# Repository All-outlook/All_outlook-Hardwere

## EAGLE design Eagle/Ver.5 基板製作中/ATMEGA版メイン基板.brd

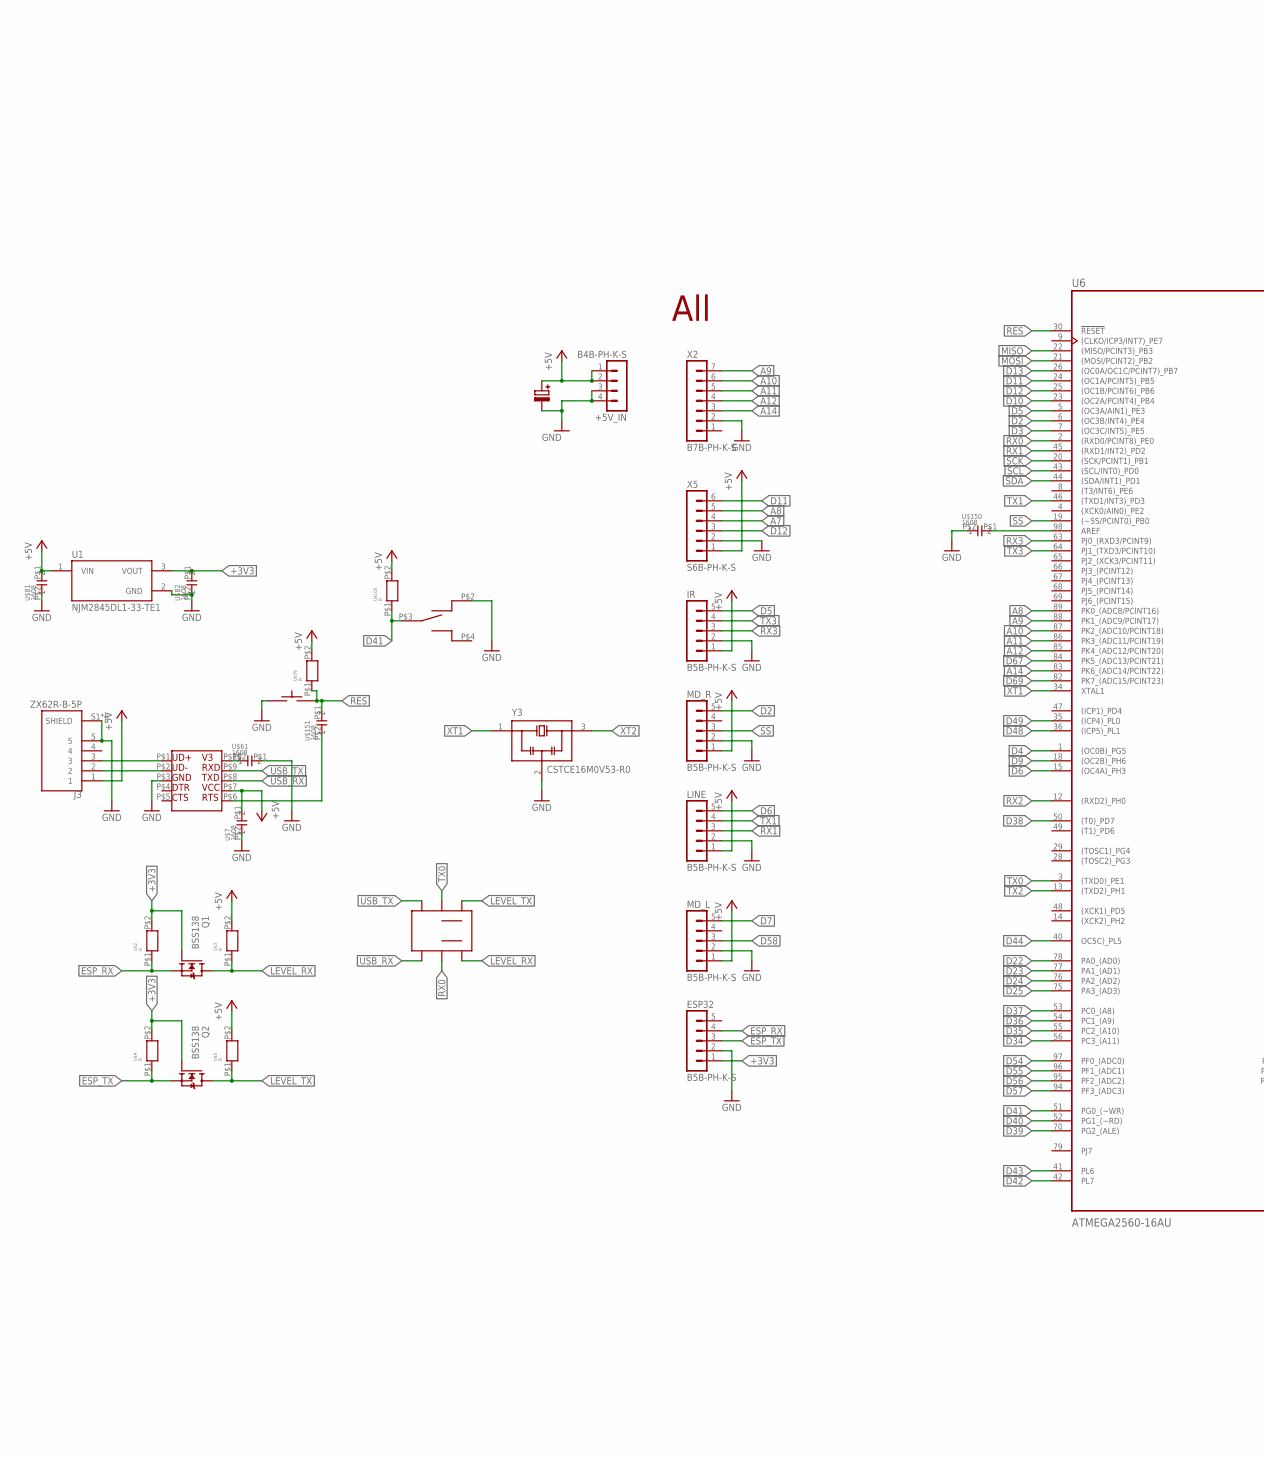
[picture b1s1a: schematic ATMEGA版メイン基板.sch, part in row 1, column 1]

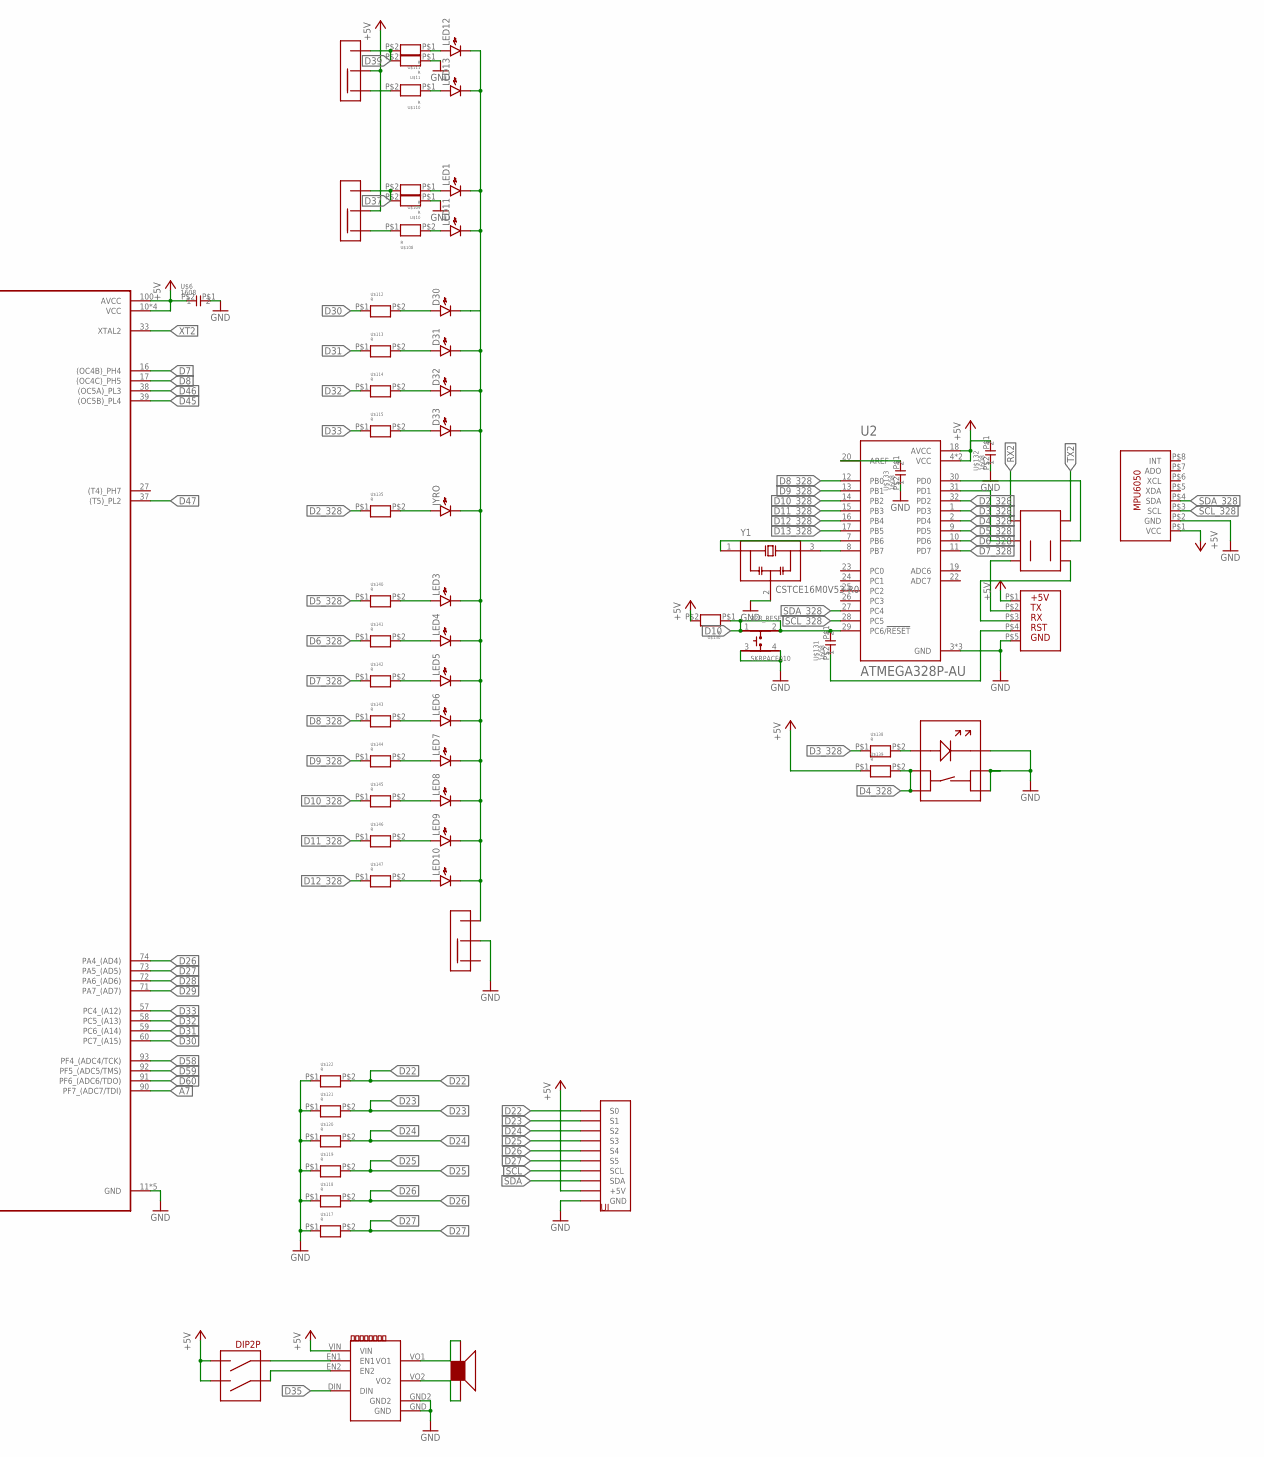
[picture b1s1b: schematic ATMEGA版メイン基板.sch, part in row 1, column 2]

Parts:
328_RESET: SKRPACE010; SW_SKRPACE010
+5V_IN: B4B-PH-K-S
D30, D31, D32, D33: LED1608
ESP32: B5B-PH-K-S
IR: B5B-PH-K-S
J3: ZX62R-B-5P; HRS_ZX62R-B-5P
JYRO: LED1608
LED1, LED3, LED4, LED5, LED6, LED7, LED8, LED9, LED10, LED11, LED12, LED13: LED1608
LINE: B5B-PH-K-S
MD_L: B5B-PH-K-S
MD_R: B5B-PH-K-S
Q1, Q2: BSS138; SOT23
U1: NJM2845DL1-33-TE1; DPAK228P968X238-4N
U2: ATMEGA328P-AU; QFP80P900X900X120-32N
U6: ATMEGA2560-16AU; QFP50P1600X1600X120-100N
U$1: 25V100
U$2, U$3, U$4, U$5, U$10, U$11, U$79, U$105, U$108, U$109, U$110, U$111, U$112, U$113, U$114, U$115, U$117, U$118, U$119, U$120, U$121, U$122, U$130, U$135, U$138, U$139, U$140, U$141, U$142, U$143, U$144, U$145, U$146, U$147: R; 1608
U$6, U$7, U$61, U$81, U$82, U$131, U$132, U$133, U$150, U$151: 1608; CON
U$8, U$136: 2SW
U$9: S
U$12: BUZA-; ぶざー
U$13: BUZA_DR
U$14: DIP2
U$46: CH340K
U$80: TAKUTO; 12
U$93: ジャイロ
U$106, U$107, U$148: SSW
U$134: SI
U$137: SWLED
U$149: UI
U$152: ALL
X2: B7B-PH-K-S
X5: S6B-PH-K-S
Y1, Y3: CSTCE16M0V53-R0; OSC_CSTCE16M0V53-R0

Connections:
+3V3: ESP32.1, Q1.1 (G), Q2.1 (G), U1.3 (VOUT), U$2.P$2, U$4.P$2, U$82.P$1 (1)
+5V: +5V_IN.1, +5V_IN.2, IR.1, J3.1, LINE.1, MD_L.1, MD_R.1, U1.1 (VIN), U2.4 (VCC), U2.6 (VCC), U2.18 (AVCC), U6.10 (VCC), U6.31 (VCC), U6.61 (VCC), U6.80 (VCC), U6.100 (AVCC), U$1.P$1, U$3.P$2, U$5.P$2, U$6.P$2 (2), U$7.P$1 (1), U$13.VIN, U$14.P$15, U$14.P$16, U$46.P$7, U$79.P$2, U$81.P$1 (1), U$93.P$1 (VCC), U$105.P$2, U$106.P$3, U$107.P$3, U$130.P$2, U$132.P$1 (1), U$134.P$1, U$139.P$1, U$149.P$1 (+5V), X5.1
A7: U6.90 (PF7_(ADC7/TDI)), X5.4
A8: U6.89 (PK0_(ADC8/PCINT16)), X5.5
A9: U6.88 (PK1_(ADC9/PCINT17)), X2.7
A10: U6.87 (PK2_(ADC10/PCINT18)), X2.6
A11: U6.86 (PK3_(ADC11/PCINT19)), X2.5
A12: U6.85 (PK4_(ADC12/PCINT20)), X2.4
A14: U6.83 (PK6_(ADC14/PCINT22)), X2.3
D2: MD_R.5, U6.6 ((OC3B/INT4)_PE4)
D2_328: U2.32 (PD2), U$135.P$1
D3: U6.7 ((OC3C/INT5)_PE5)
D3_328: U2.1 (PD3), U$138.P$1
D4: U6.1 ((OC0B)_PG5)
D4_328: U2.2 (PD4), U$137.1, U$137.2, U$139.P$2
D5: IR.5, U6.5 ((OC3A/AIN1)_PE3)
D5_328: U2.9 (PD5), U$140.P$1
D6: LINE.5, U6.15 ((OC4A)_PH3)
D6_328: U2.10 (PD6), U$141.P$1
D7: MD_L.5, U6.16 ((OC4B)_PH4)
D7_328: U2.11 (PD7), U$142.P$1
D8: U6.17 ((OC4C)_PH5)
D8_328: U2.12 (PB0), U$143.P$1
D9: U6.18 ((OC2B)_PH6)
D9_328: U2.13 (PB1), U$144.P$1
D10: 328_RESET.1, 328_RESET.2, U2.29 (PC6/!RESET), U6.23 ((OC2A/PCINT4)_PB4), U$130.P$1, U$131.P$1 (1)
D10_328: U2.14 (PB2), U$145.P$1
D11: U6.24 ((OC1A/PCINT5)_PB5), X5.6
D11_328: U2.15 (PB3), U$146.P$1
D12: U6.25 ((OC1B/PCINT6)_PB6), X5.3
D12_328: U2.16 (PB4), U$147.P$1
D13: U6.26 ((OC0A/OC1C/PCINT7)_PB7)
D13_328: U2.17 (PB5)
D22: U6.78 (PA0_(AD0)), U$122.P$2, U$149.P$3 (S0)
D23: U6.77 (PA1_(AD1)), U$121.P$2, U$149.P$4 (S1)
D24: U6.76 (PA2_(AD2)), U$120.P$2, U$149.P$5 (S2)
D25: U6.75 (PA3_(AD3)), U$119.P$2, U$149.P$6 (S3)
D26: U6.74 (PA4_(AD4)), U$118.P$2, U$149.P$7 (S4)
D27: U6.73 (PA5_(AD5)), U$117.P$2, U$149.P$8 (S5)
D28: U6.72 (PA6_(AD6))
D29: U6.71 (PA7_(AD7))
D30: U6.60 (PC7_(A15)), U$112.P$1
D31: U6.59 (PC6_(A14)), U$113.P$1
D32: U6.58 (PC5_(A13)), U$114.P$1
D33: U6.57 (PC4_(A12)), U$115.P$1
D34: U6.56 (PC3_(A11))
D35: U6.55 (PC2_(A10)), U$13.DIN
D36: U6.54 (PC1_(A9))
D37: U6.53 (PC0_(A8)), U$10.P$2, U$106.P$2, U$109.P$2
D38: U6.50 ((T0)_PD7)
D39: U6.70 (PG2_(ALE)), U$11.P$2, U$107.P$2, U$111.P$2
D40: U6.52 (PG1_(~RD))
D41: U6.51 (PG0_(~WR)), U$9.P$3 (2), U$105.P$1
D42: U6.42 (PL7)
D43: U6.41 (PL6)
D44: U6.40 (OC5C)_PL5)
D45: U6.39 ((OC5B)_PL4)
D46: U6.38 ((OC5A)_PL3)
D47: U6.37 ((T5)_PL2)
D48: U6.36 ((ICP5)_PL1)
D49: U6.35 ((ICP4)_PL0)
D54: U6.97 (PF0_(ADC0))
D55: U6.96 (PF1_(ADC1))
D56: U6.95 (PF2_(ADC2))
D57: U6.94 (PF3_(ADC3))
D58: MD_L.3, U6.93 (PF4_(ADC4/TCK))
D59: U6.92 (PF5_(ADC5/TMS))
D60: U6.91 (PF6_(ADC6/TDO))
D67: U6.84 (PK5_(ADC13/PCINT21))
D69: U6.82 (PK7_(ADC15/PCINT23))
ESP_RX: ESP32.4, Q1.2 (S), U$2.P$1
ESP_TX: ESP32.3, Q2.2 (S), U$4.P$1
GND: 328_RESET.3, 328_RESET.4, +5V_IN.3, +5V_IN.4, ESP32.2, IR.2, J3.5, J3.S1 (SHIELD), J3.S2 (SHIELD), J3.S3 (SHIELD), J3.S4 (SHIELD), J3.S5 (SHIELD), J3.S6 (SHIELD), LINE.2, MD_L.2, MD_R.2, U1.2 (GND), U2.3 (GND), U2.5 (GND), U2.21 (GND), U6.11 (GND), U6.32 (GND), U6.62 (GND), U6.81 (GND), U6.99 (GND), U$1.P$2, U$6.P$1 (1), U$7.P$2 (2), U$9.P$2 (1), U$10.P$1, U$11.P$1, U$13.GND, U$13.GND2, U$46.P$3, U$61.P$1 (1), U$80.P$1, U$80.P$4, U$81.P$2 (2), U$82.P$2 (2), U$93.P$2 (GND), U$117.P$1, U$118.P$1, U$119.P$1, U$120.P$1, U$121.P$1, U$122.P$1, U$132.P$2 (2), U$133.P$2 (2), U$134.P$5, U$137.3, U$137.4, U$137.- (LED-), U$148.P$3, U$149.P$2 (GND), U$150.P$2 (2), X2.2, X5.2, Y1.2 (GND), Y3.2 (GND)
LEVEL_RX: Q1.3 (D), U$3.P$1, U$8.P$1
LEVEL_TX: Q2.3 (D), U$5.P$1, U$8.P$6
MISO: U6.22 ((MISO/PCINT3)_PB3)
MOSI: U6.21 ((MOSI/PCINT2)_PB2)
unnamed: U$12.P$2, U$13.VO2
unnamed: J3.2, U$46.P$2
unnamed: J3.3, U$46.P$1
unnamed: U$46.P$10, U$61.P$2 (2)
unnamed: D30.K, D31.K, D32.K, D33.K, JYRO.K, LED1.K, LED3.K, LED4.K, LED5.K, LED6.K, LED7.K, LED8.K, LED9.K, LED10.K, LED11.K, LED12.K, LED13.K, U$148.P$2
unnamed: LED12.A, U$111.P$1
unnamed: LED13.A, U$110.P$1
unnamed: U$107.P$1, U$110.P$2
unnamed: U$106.P$1, U$108.P$1
unnamed: LED11.A, U$108.P$2
unnamed: LED1.A, U$109.P$1
unnamed: U$12.P$1, U$13.VO1
unnamed: U$13.EN2, U$14.P$1
unnamed: U$13.EN1, U$14.P$2
unnamed: D30.A, U$112.P$2
unnamed: D31.A, U$113.P$2
unnamed: D32.A, U$114.P$2
unnamed: D33.A, U$115.P$2
unnamed: U2.20 (AREF), U$133.P$1 (1)
unnamed: U$131.P$2 (2), U$134.P$4
unnamed: U2.31 (PD1), U$136.P$2
unnamed: U2.8 (PB7), Y1.3 (OUT)
unnamed: U2.7 (PB6), Y1.1 (IN)
unnamed: JYRO.A, U$135.P$2
unnamed: U2.30 (PD0), U$136.P$5
unnamed: U$134.P$3, U$136.P$6
unnamed: U$134.P$2, U$136.P$1
unnamed: U$137.+ (LED+), U$138.P$2
unnamed: LED3.A, U$140.P$2
unnamed: LED4.A, U$141.P$2
unnamed: LED5.A, U$142.P$2
unnamed: LED6.A, U$143.P$2
unnamed: LED7.A, U$144.P$2
unnamed: LED8.A, U$145.P$2
unnamed: LED9.A, U$146.P$2
unnamed: LED10.A, U$147.P$2
unnamed: U6.98 (AREF), U$150.P$1 (1)
unnamed: U$46.P$6, U$151.P$2 (2)
RES: U6.30 (!RESET), U$79.P$1, U$80.P$2, U$80.P$3, U$151.P$1 (1)
RX0: U6.2 ((RXD0/PCINT8)_PE0), U$8.P$2
RX1: LINE.3, U6.45 ((RXD1/INT2)_PD2)
RX2: U6.12 ((RXD2)_PH0), U$136.P$3
RX3: IR.3, U6.63 (PJ0_(RXD3/PCINT9))
SCK: U6.20 ((SCK/PCINT1)_PB1)
SCL: U6.43 ((SCL/INT0)_PD0), U$149.P$9 (SCL)
SCL_328: U2.28 (PC5), U$93.P$3 (SCL)
SDA: U6.44 ((SDA/INT1)_PD1), U$149.P$10 (SDA)
SDA_328: U2.27 (PC4), U$93.P$4 (SDA)
SS: MD_R.3, U6.19 ((~SS/PCINT0)_PB0)
TX0: U6.3 ((TXD0)_PE1), U$8.P$5
TX1: LINE.4, U6.46 ((TXD1/INT3)_PD3)
TX2: U6.13 ((TXD2)_PH1), U$136.P$4
TX3: IR.4, U6.64 (PJ1_(TXD3/PCINT10))
USB_RX: U$8.P$3, U$46.P$8
USB_TX: U$8.P$4, U$46.P$9
XT1: U6.34 (XTAL1), Y3.1 (IN)
XT2: U6.33 (XTAL2), Y3.3 (OUT)

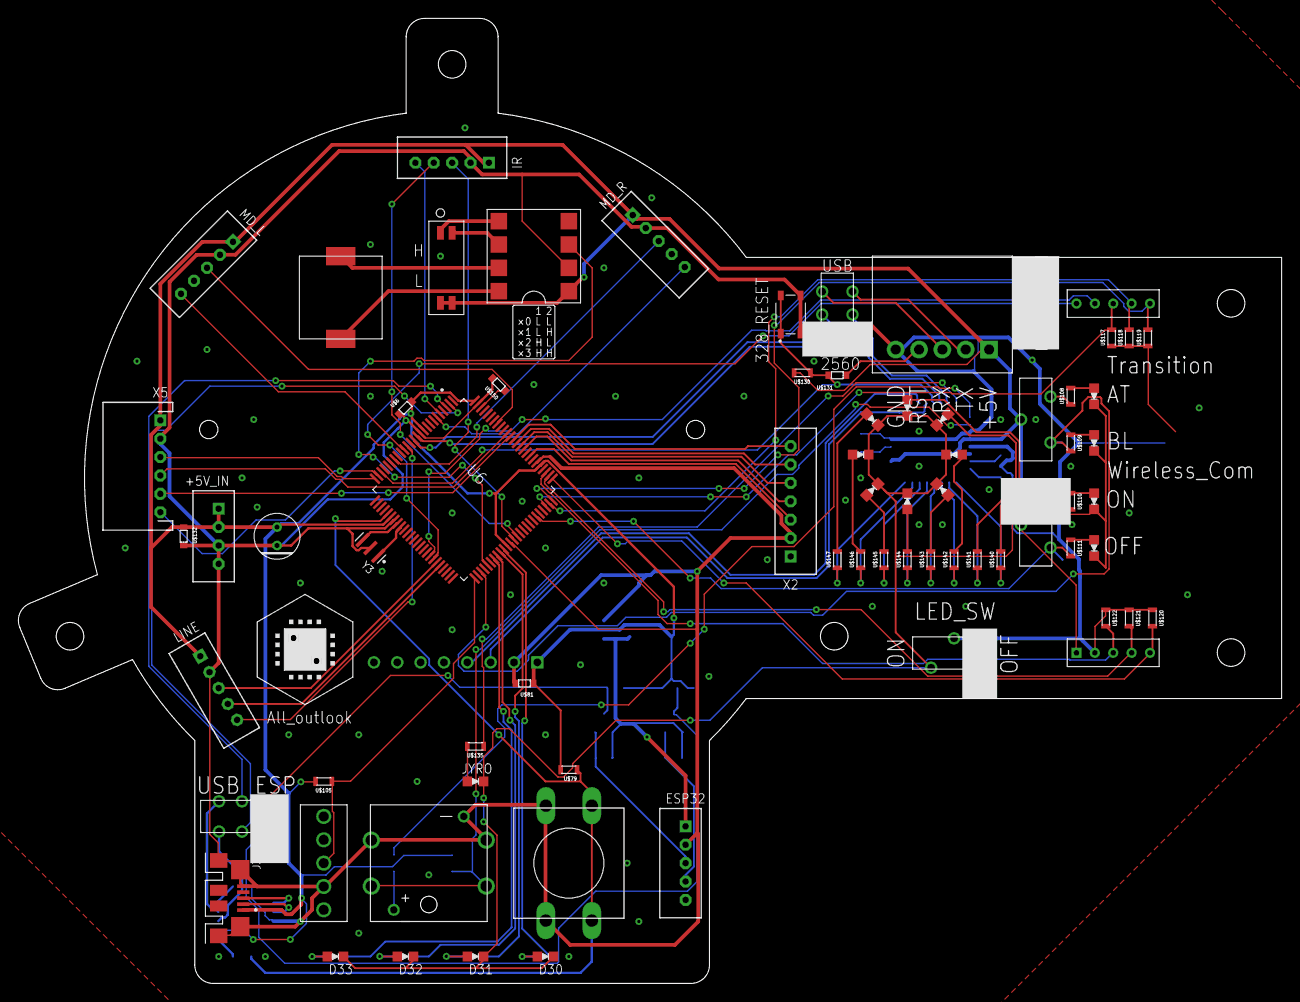
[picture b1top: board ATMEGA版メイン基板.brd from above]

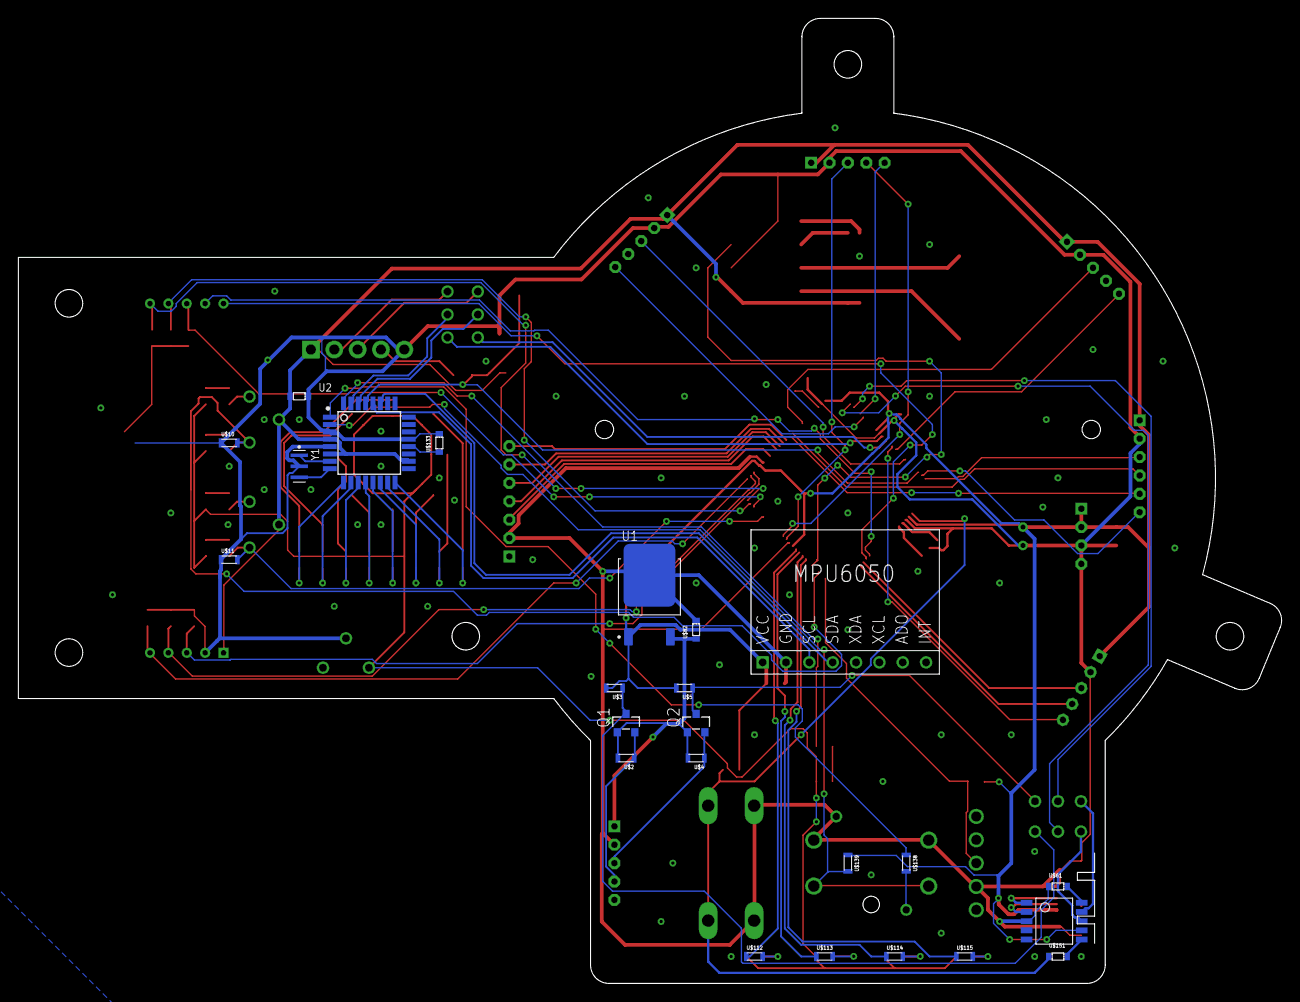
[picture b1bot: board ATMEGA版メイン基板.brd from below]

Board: 2 copper layers, 137.4 x 105.0 mm, 95 parts (24 on the bottom side), 103 nets.

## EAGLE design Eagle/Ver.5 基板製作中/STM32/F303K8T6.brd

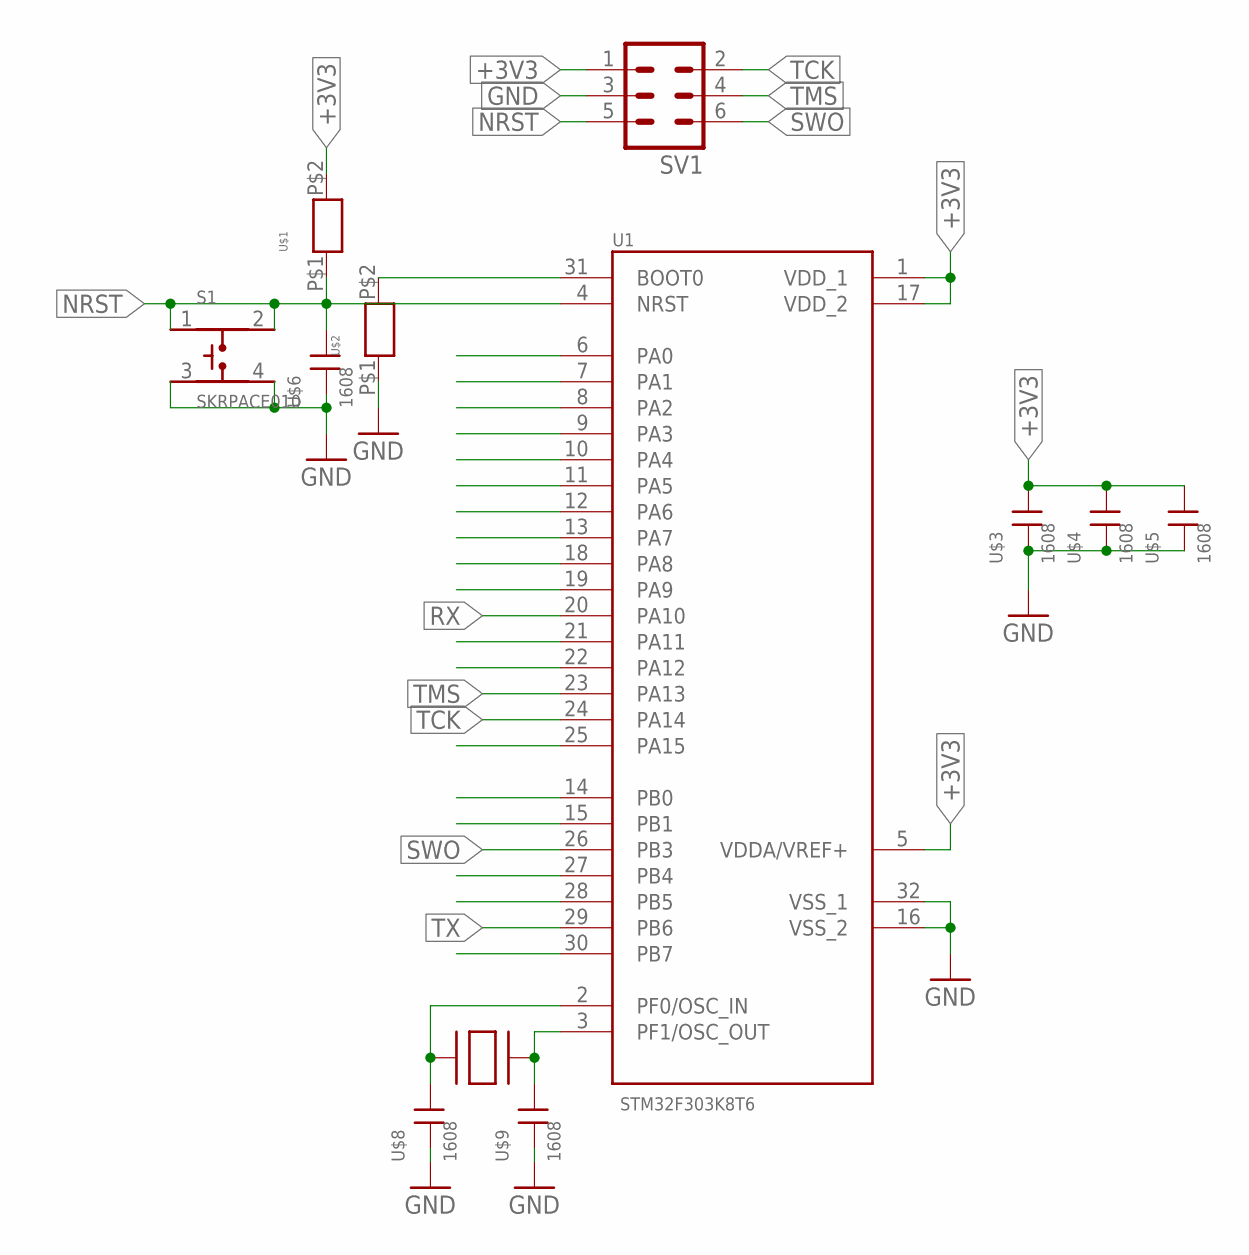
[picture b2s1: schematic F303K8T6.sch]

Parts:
S1: SKRPACE010; SW_SKRPACE010
SV1: ML6
U1: STM32F303K8T6; QFP80P900X900X160-32N
U$1, U$2: R; 1608
U$3, U$4, U$5, U$6, U$8, U$9: 1608; CON
U$7: SUISYOU; 水晶

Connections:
+3V3: SV1.1, U1.1 (VDD_1), U1.5 (VDDA/VREF+), U1.17 (VDD_2), U$1.P$2, U$3.P$1 (1), U$4.P$1 (1), U$5.P$1 (1)
GND: S1.3, S1.4, SV1.3, U1.16 (VSS_2), U1.32 (VSS_1), U$2.P$1, U$3.P$2 (2), U$4.P$2 (2), U$5.P$2 (2), U$6.P$2 (2), U$8.P$2 (2), U$9.P$2 (2)
unnamed: U1.31 (BOOT0), U$2.P$2
unnamed: U1.2 (PF0/OSC_IN), U$7.P$1, U$8.P$1 (1)
unnamed: U1.3 (PF1/OSC_OUT), U$7.P$2, U$9.P$1 (1)
NRST: S1.1, S1.2, SV1.5, U1.4 (NRST), U$1.P$1, U$6.P$1 (1)
RX: U1.20 (PA10)
SWO: SV1.6, U1.26 (PB3)
TCK: SV1.2, U1.24 (PA14)
TMS: SV1.4, U1.23 (PA13)
TX: U1.29 (PB6)

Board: 2 copper layers, 12 parts (0 on the bottom side), 9 nets, no tracks yet.

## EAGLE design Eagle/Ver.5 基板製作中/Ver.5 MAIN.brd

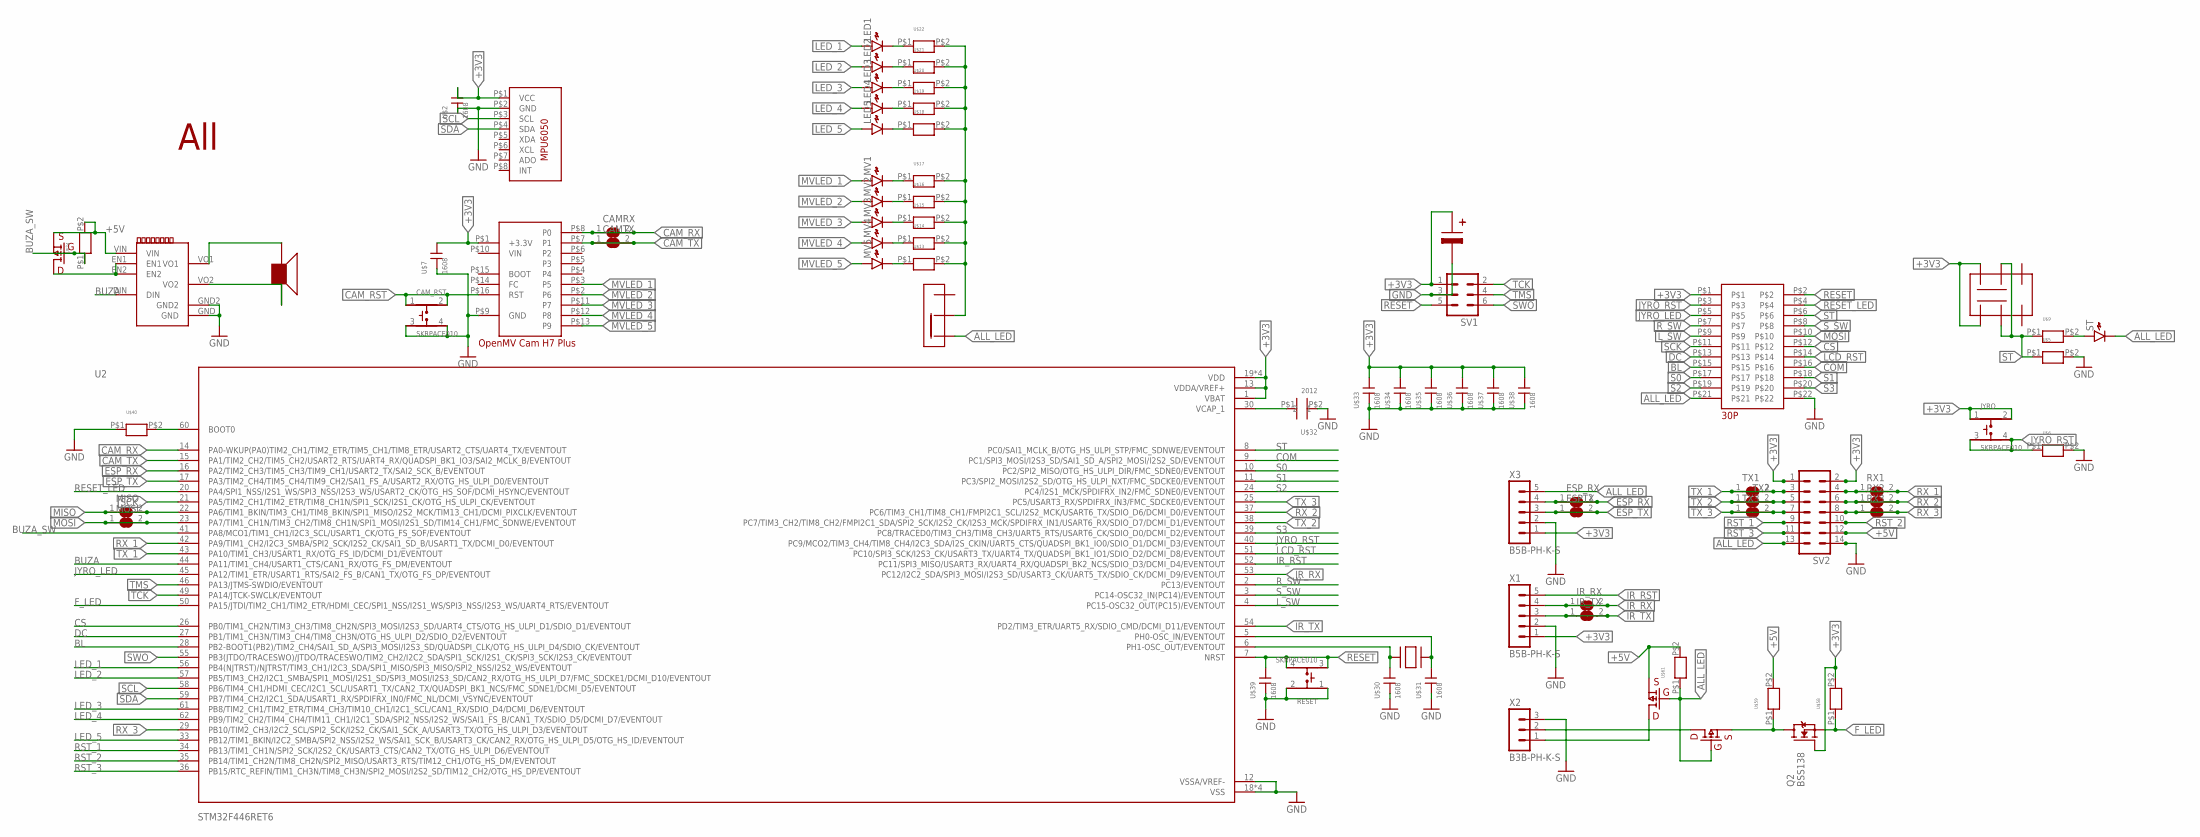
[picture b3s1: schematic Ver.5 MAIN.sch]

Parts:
CAMRX: SJ
CAMTX: SJ
CAM_RST: SKRPACE010; SW_SKRPACE010
ESPTX: SJ
ESP_RX: SJ
IR_RX: SJ
IR_TX: SJ
JYRO: SKRPACE010; SW_SKRPACE010
LED1, LED2, LED3, LED4, LED5: LED1608
MISO: SJ
MOSI: SJ
MV1, MV2, MV3, MV4, MV5: LED1608
Q2: BSS138; SOT23
RESET: SKRPACE010; SW_SKRPACE010
RX1, RX2, RX3: SJ
ST: LED1608
SV1: ML6L
SV2: ML14L
TX1, TX2, TX3: SJ
U2: STM32F446RET6; QFP50P1200X1200X160-64N
U$1: OPENMV
U$2, U$7, U$30, U$31, U$33, U$34, U$35, U$36, U$37, U$38, U$39: 1608; CON
U$3: ジャイロ
U$4: LPRP; LPRO
U$5, U$6, U$9, U$13, U$14, U$15, U$16, U$17, U$18, U$19, U$20, U$21, U$22, U$24, U$40, U$58, U$59, U$61: R; 1608
U$8: 22SW; ２２ｓｗ
U$10: SSW
U$11: BUZA_DR
U$12: BUZA-; ぶざー
U$23, U$60, U$62: 808
U$25: 10
U$26: ALL
U$29: SUISYOU; 水晶
U$32: 2012
X1, X3: B5B-PH-K-S
X2: B3B-PH-K-S

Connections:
+3V3: JYRO.1, JYRO.2, Q2.1 (G), SV1.1, SV2.1, SV2.2, U2.1 (VBAT), U2.13 (VDDA/VREF+), U2.19 (VDD), U2.32 (VDD), U2.48 (VDD), U2.64 (VDD), U$1.P$1 (+3.3V), U$2.P$1 (1), U$3.P$1 (VCC), U$4.P$1, U$7.P$1 (1), U$8.P$1, U$8.P$4, U$25.P$1, U$33.P$1 (1), U$34.P$1 (1), U$35.P$1 (1), U$36.P$1 (1), U$37.P$1 (1), U$38.P$1 (1), U$58.P$2, X1.1, X3.1
+5V: SV2.12, U$11.VIN, U$23.S, U$24.P$2, U$59.P$2, U$60.S, U$61.P$2
+5V_OFF1: U$60.D, U$60.DD (D), U$60.DDD (D), U$60.DDDD (D), X2.1
ALL_LED: ST.K, SV2.13, U$4.P$21, U$10.P$1, U$60.G, U$61.P$1, U$62.G, X3.5
BL: U2.28 (PB2-BOOT1(PB2)/TIM2_CH4/SAI1_SD_A/SPI3_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), U$4.P$15
BUZA: U2.44 (PA11/TIM1_CH4/USART1_CTS/CAN1_RX/OTG_FS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), U$11.DIN
BUZA_SW: U2.41 (PA8/MCO1/TIM1_CH1/I2C3_SCL/USART1_CK/OT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), U$23.G, U$24.P$1
CAM_RST: CAM_RST.1, CAM_RST.2, U$1.P$16 (RST)
CAM_RX: CAMRX.1, CAMRX.2, U2.14 (PA0-WKUP(PA0)TIM2_CH1/TIM2_ETR/TIM5_CH1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), U$1.P$8 (P0)
CAM_TX: CAMTX.1, CAMTX.2, U2.15 (PA1/TIM2_CH2/TIM5_CH2/USART2_RTS/UART4_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), U$1.P$7 (P1)
COM: U2.9 (PC1/SPI3_MOSI/I2S3_SD/SAI1_SD_A/SPI2_MO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), U$4.P$16
CS: U2.26 (PB0/TIM1_CH2N/TIM3_CH3/TIM8_CH2N/SPI3_M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), U$4.P$12
DC: U2.27 (PB1/TIM1_CH3N/TIM3_CH4/TIM8_CH3N/OTG_HS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), U$4.P$13
ESP_RX: ESP_RX.1, ESP_RX.2, U2.16 (PA2/TIM2_CH3/TIM5_CH3/TIM9_CH1/USART2_T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), X3.4
ESP_TX: ESPTX.1, ESPTX.2, U2.17 (PA3/TIM2_CH4/TIM5_CH4/TIM9_CH2/SAI1_FS_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), X3.3
F_LED: Q2.2 (S), U2.50 (PA15/JTDI/TIM2_CH1/TIM2_ETR/HDMI_CEC/SP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), U$58.P$1
GND: CAM_RST.3, CAM_RST.4, RESET.1, RESET.2, SV1.3, SV2.14, U2.12 (VSSA/VREF-), U2.18 (VSS), U2.31 (VSS), U2.47 (VSS), U2.63 (VSS), U$1.P$9 (GND), U$2.P$2 (2), U$3.P$2 (GND), U$4.P$22, U$5.P$2, U$6.P$2, U$7.P$2 (2), U$11.GND, U$11.GND2, U$25.P$2, U$30.P$2 (2), U$31.P$2 (2), U$32.P$2 (2), U$33.P$2 (2), U$34.P$2 (2), U$35.P$2 (2), U$36.P$2 (2), U$37.P$2 (2), U$38.P$2 (2), U$39.P$2 (2), U$40.P$1, X1.2, X2.3, X3.2
IR_RST: U2.52 (PC11/SPI3_MISO/USART3_RX/UART4_RX/QUADS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), X1.5
IR_RX: IR_RX.1, IR_RX.2, U2.53 (PC12/I2C2_SDA/SPI3_MOSI/I2S3_SD/USART3_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), X1.4
IR_TX: IR_TX.1, IR_TX.2, U2.54 (PD2/TIM3_ETR/UART5_RX/SDIO_CMD/DCMI_D11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), X1.3
JYRO_LED: U2.45 (PA12/TIM1_ETR/USART1_RTS/SAI2_FS_B/CAN1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), U$4.P$5
JYRO_RST: JYRO.3, JYRO.4, U2.40 (PC9/MCO2/TIM3_CH4/TIM8_CH4/I2C3_SDA/I2S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), U$4.P$3, U$6.P$1
LCD_RST: U2.51 (PC10/SPI3_SCK/I2S3_CK/USART3_TX/UART4_T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), U$4.P$14
LED_1: LED1.A, U2.56 (PB4(NJTRST)/NJTRST/TIM3_CH1/I2C3_SDA/SP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)
LED_2: LED2.A, U2.57 (PB5/TIM3_CH2/I2C1_SMBA/SPI1_MOSI/I2S1_S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)
LED_3: LED3.A, U2.61 (PB8/TIM2_CH1/TIM2_ETR/TIM4_CH3/TIM10_CH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)
LED_4: LED4.A, U2.62 (PB9/TIM2_CH2/TIM4_CH4/TIM11_CH1/I2C1_SD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)
LED_5: LED5.A, U2.33 (PB12/TIM1_BKIN/I2C2_SMBA/SPI2_NSS/I2S2_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)
L_SW: U2.4 (PC15-OSC32_OUT(PC15)/EVENTOUT), U$4.P$9
MISO: MISO.1, MISO.2, U2.22 (PA6/TIM1_BKIN/TIM3_CH1/TIM8_BKIN/SPI1_M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)
MOSI: MOSI.1, MOSI.2, U2.23 (PA7/TIM1_CH1N/TIM3_CH2/TIM8_CH1N/SPI1_M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), U$4.P$10
MVLED_1: MV1.A, U$1.P$3 (P5)
MVLED_2: MV2.A, U$1.P$2 (P6)
MVLED_3: MV3.A, U$1.P$11 (P7)
MVLED_4: MV4.A, U$1.P$12 (P8)
MVLED_5: MV5.A, U$1.P$13 (P9)
unnamed: U$62.D, U$62.DD (D), U$62.DDD (D), U$62.DDDD (D), X2.2
unnamed: U$11.VO1, U$12.P$1
unnamed: U$11.VO2, U$12.P$2
unnamed: U$11.EN1, U$11.EN2, U$23.D, U$23.DD (D), U$23.DDD (D), U$23.DDDD (D)
unnamed: ST.A, U$9.P$2
unnamed: U$10.P$3, U$13.P$2, U$14.P$2, U$15.P$2, U$16.P$2, U$17.P$2, U$18.P$2, U$19.P$2, U$20.P$2, U$21.P$2, U$22.P$2
unnamed: LED1.K, U$22.P$1
unnamed: LED2.K, U$21.P$1
unnamed: LED3.K, U$20.P$1
unnamed: LED4.K, U$19.P$1
unnamed: LED5.K, U$18.P$1
unnamed: MV5.K, U$13.P$1
unnamed: MV4.K, U$14.P$1
unnamed: MV3.K, U$15.P$1
unnamed: MV2.K, U$16.P$1
unnamed: MV1.K, U$17.P$1
unnamed: U2.6 (PH1-OSC_OUT/EVENTOUT), U$29.P$1, U$30.P$1 (1)
unnamed: U2.5 (PH0-OSC_IN/EVENTOUT), U$29.P$2, U$31.P$1 (1)
unnamed: Q2.3 (D), U$59.P$1, U$62.S
unnamed: U2.30 (VCAP_1), U$32.P$1 (1)
unnamed: U2.60 (BOOT0), U$40.P$2
RESET: RESET.3, RESET.4, SV1.5, U2.7 (NRST), U$4.P$2, U$39.P$1 (1)
RESET_LED: U2.20 (PA4/SPI1_NSS/I2S1_WS/SPI3_NSS/I2S3_WS/U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), U$4.P$4
RST_1: SV2.9, U2.34 (PB13/TIM1_CH1N/SPI2_SCK/I2S2_CK/USART3_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)
RST_2: SV2.10, U2.35 (PB14/TIM1_CH2N/TIM8_CH2N/SPI2_MISO/USAR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)
RST_3: SV2.11, U2.36 (PB15/RTC_REFIN/TIM1_CH3N/TIM8_CH3N/SPI2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)
RX_1: RX1.1, RX1.2, SV2.4, U2.42 (PA9/TIM1_CH2/I2C3_SMBA/SPI2_SCK/I2S2_CK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)
RX_2: RX2.1, RX2.2, SV2.6, U2.37 (PC6/TIM3_CH1/TIM8_CH1/FMPI2C1_SCL/I2S2_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)
RX_3: RX3.1, RX3.2, SV2.8, U2.29 (PB10/TIM2_CH3/I2C2_SCL/SPI2_SCK/I2S2_CK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)
R_SW: U2.2 (PC13/EVENTOUT), U$4.P$7
S0: U2.10 (PC2/SPI2_MISO/OTG_HS_ULPI_DIR/FMC_SDNE0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), U$4.P$17
S1: U2.11 (PC3/SPI2_MOSI/I2S2_SD/OTG_HS_ULPI_NXT/F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), U$4.P$18
S2: U2.24 (PC4/I2S1_MCK/SPDIFRX_IN2/FMC_SDNE0/EVEN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), U$4.P$19
S3: U2.39 (PC8/TRACED0/TIM3_CH3/TIM8_CH3/UART5_RTS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), U$4.P$20
SCK: U2.21 (PA5/TIM2_CH1/TIM2_ETR/TIM8_CH1N/SPI1_SC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), U$4.P$11
SCL: U2.58 (PB6/TIM4_CH1/HDMI_CEC/I2C1_SCL/USART1_T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), U$3.P$3 (SCL)
SDA: U2.59 (PB7/TIM4_CH2/I2C1_SDA/USART1_RX/SPDIFRX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), U$3.P$4 (SDA)
ST: U2.8 (PC0/SAI1_MCLK_B/OTG_HS_ULPI_STP/FMC_SDN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), U$4.P$6, U$5.P$1, U$8.P$2, U$8.P$5, U$9.P$1
SWO: SV1.6, U2.55 (PB3(JTDO/TRACESWO)/JTDO/TRACESWO/TIM2_C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)
S_SW: U2.3 (PC14-OSC32_IN(PC14)/EVENTOUT), U$4.P$8
TCK: SV1.2, U2.49 (PA14/JTCK-SWCLK/EVENTOUT)
TMS: SV1.4, U2.46 (PA13/JTMS-SWDIO/EVENTOUT)
TX_1: SV2.3, TX1.1, TX1.2, U2.43 (PA10/TIM1_CH3/USART1_RX/OTG_FS_ID/DCMI_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)
TX_2: SV2.5, TX2.1, TX2.2, U2.38 (PC7/TIM3_CH2/TIM8_CH2/FMPI2C1_SDA/SPI2_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)
TX_3: SV2.7, TX3.1, TX3.2, U2.25 (PC5/USART3_RX/SPDIFRX_IN3/FMC_SDCKE0/EV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)

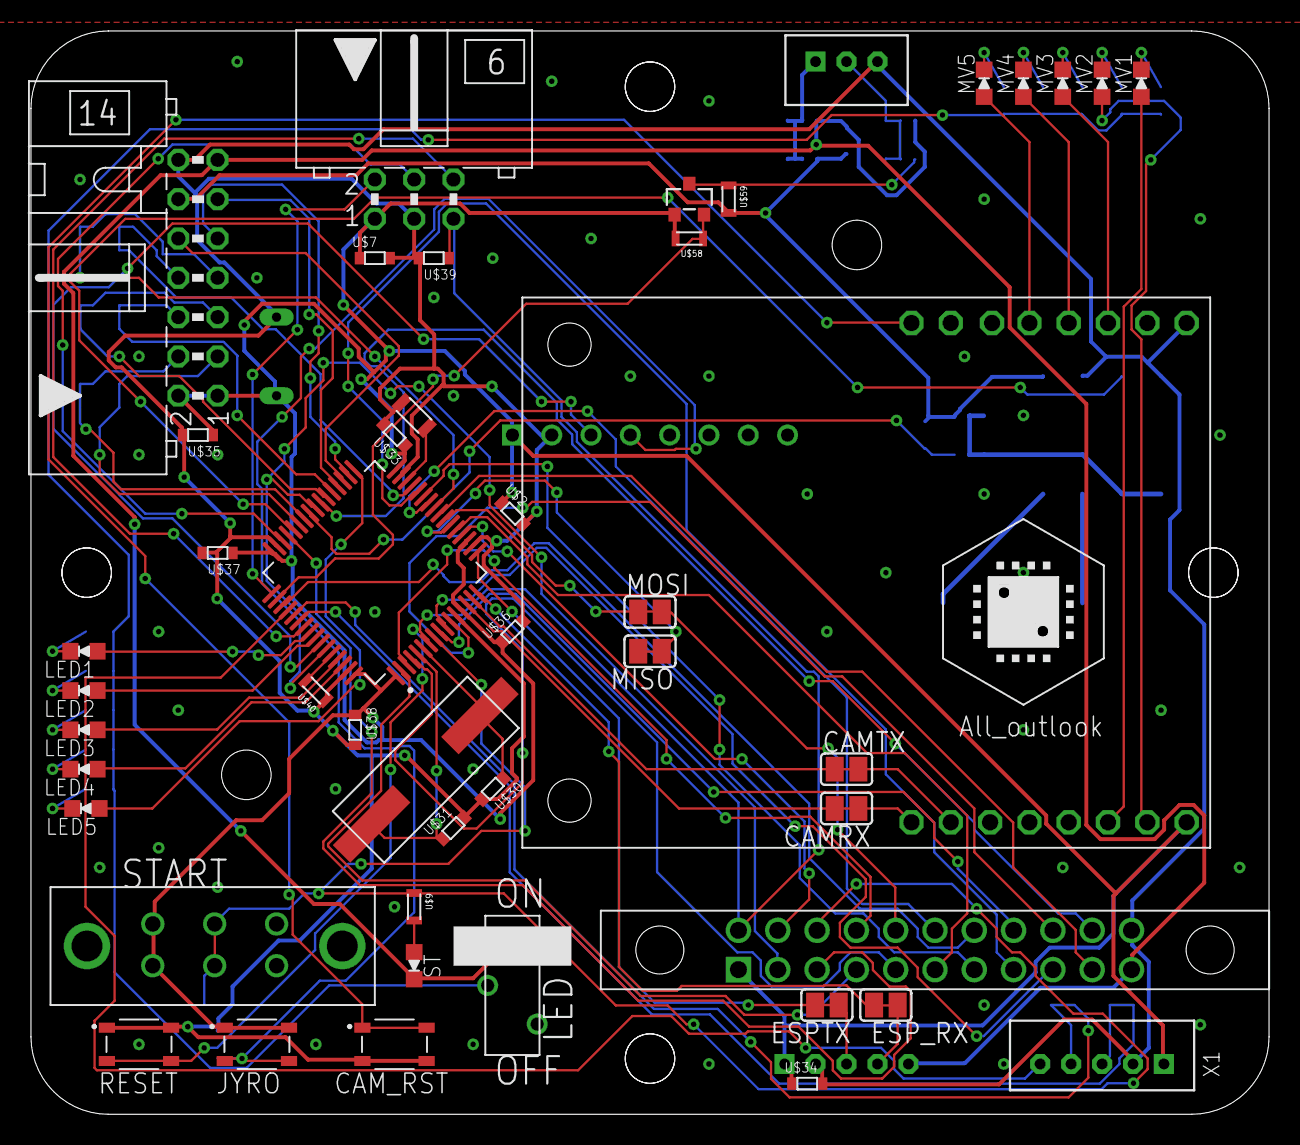
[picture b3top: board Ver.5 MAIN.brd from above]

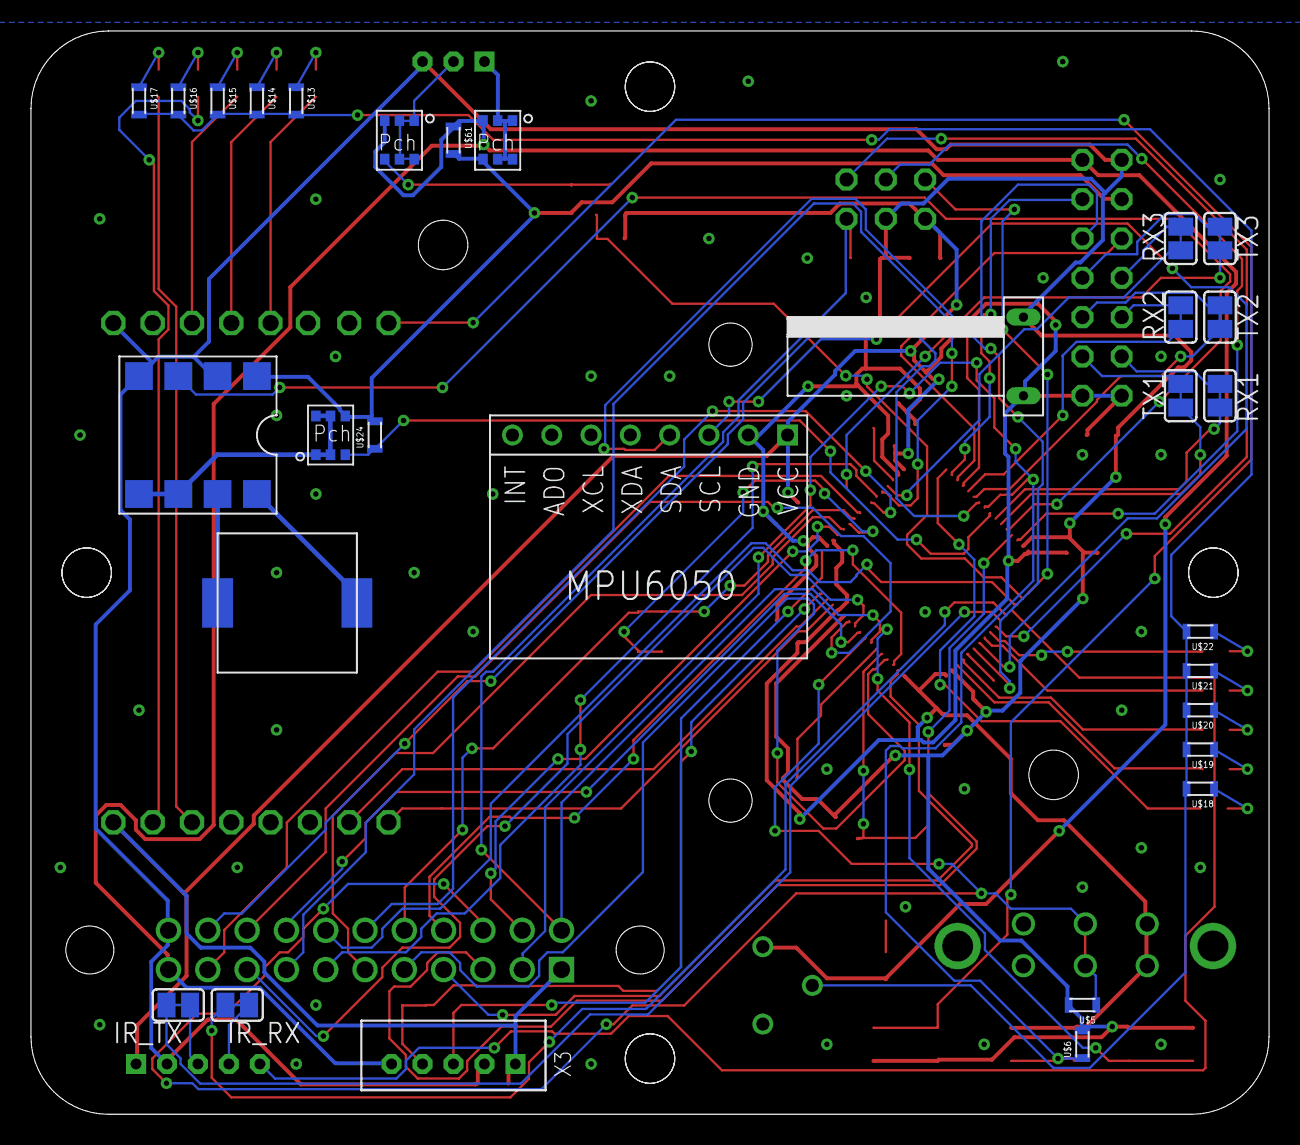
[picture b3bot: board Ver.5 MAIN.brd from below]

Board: 2 copper layers, 80.0 x 70.0 mm, 78 parts (30 on the bottom side), 81 nets.
